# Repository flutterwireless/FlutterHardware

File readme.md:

Flutter Wireless Open Source Hardware files
==============

Flutter Wireless is an open source hardware platform designed by Taylor Alexander for the development of mesh networking protocols and connected devices. It is intended for use in robotics, hobbyist, commercial, or educational applications. For more information visit [FlutterWireless.com](http://www.flutterwireless.com/). All files copyright Flutter Wireless, 2013-2015.

Instructions
----------

If you want to modify these files, you need a version of EagleCAD that can work with 4 layer files (the freeware version only supports 2 layers). They have a [hobby license](http://www.cadsoftusa.com/shop/eagle-hobbyist-and-education/?lang=en) that is well-suited for this. If you only want to reproduce the boards as is, we have provided gerber files. Note that the files do not have a clean perimeter as they are intended to be arrayed on a panel. We will probably revert to a non panel-ready version at some point, as I don't believe our assembler needs them to be that way. Please file an issue if you cannot use them in their current format.

License
--------

This is the initial release of the hardware design files. They are licensed under Creative Commons Attribution-ShareAlike 4.0 International (CC BY-SA 4.0), which is available at: http://creativecommons.org/licenses/by-sa/4.0/
If you use the files, please check them carefully - they may contain errors.

Legal
--------

These documents are provided for informational purposes only and neither Flutter Wireless nor its employees, contributors, or representatives may be held liable for any damages caused by the use of these files. By using these files, you agree to release from all liability and hold harmless Flutter Wireless, its employees, contributors, and representatives. We are not responsible for any errors or ommissions contained herin, and all devices derived from this work should be indepentently verified by an engineer or engineers skilled in the appropriate fields.

The devices described by these files are wireless devices classified as intentional radiators. The electromagnetic spectrum used by these devices is a publicly shared medium that is regulated by all governments worldwide. If you produce your own copies of these boards, you must comply with all local wireless regulations including but not limited to passing wireless certification tests. Flutter Wireless has performed wireless testing to permit us to distribute this hardware in various regions, but this certification is exclusive to Flutter Wireless and does not extend to third party manufacturers. It is your responsibility to know the laws and ensure that devices you produce follow them.

It should also be noted that open source radio products are a new phenomenon. So far the law permits them, but there is a risk that new legal restrictions could be passed that harm the open source community if users abuse this hardware by producing versions of this or other hardware that violate the law. Be respectful and responsible - don't make changes that you don't understand or that violate the law. None of this should be considered legal advice - just common sense.

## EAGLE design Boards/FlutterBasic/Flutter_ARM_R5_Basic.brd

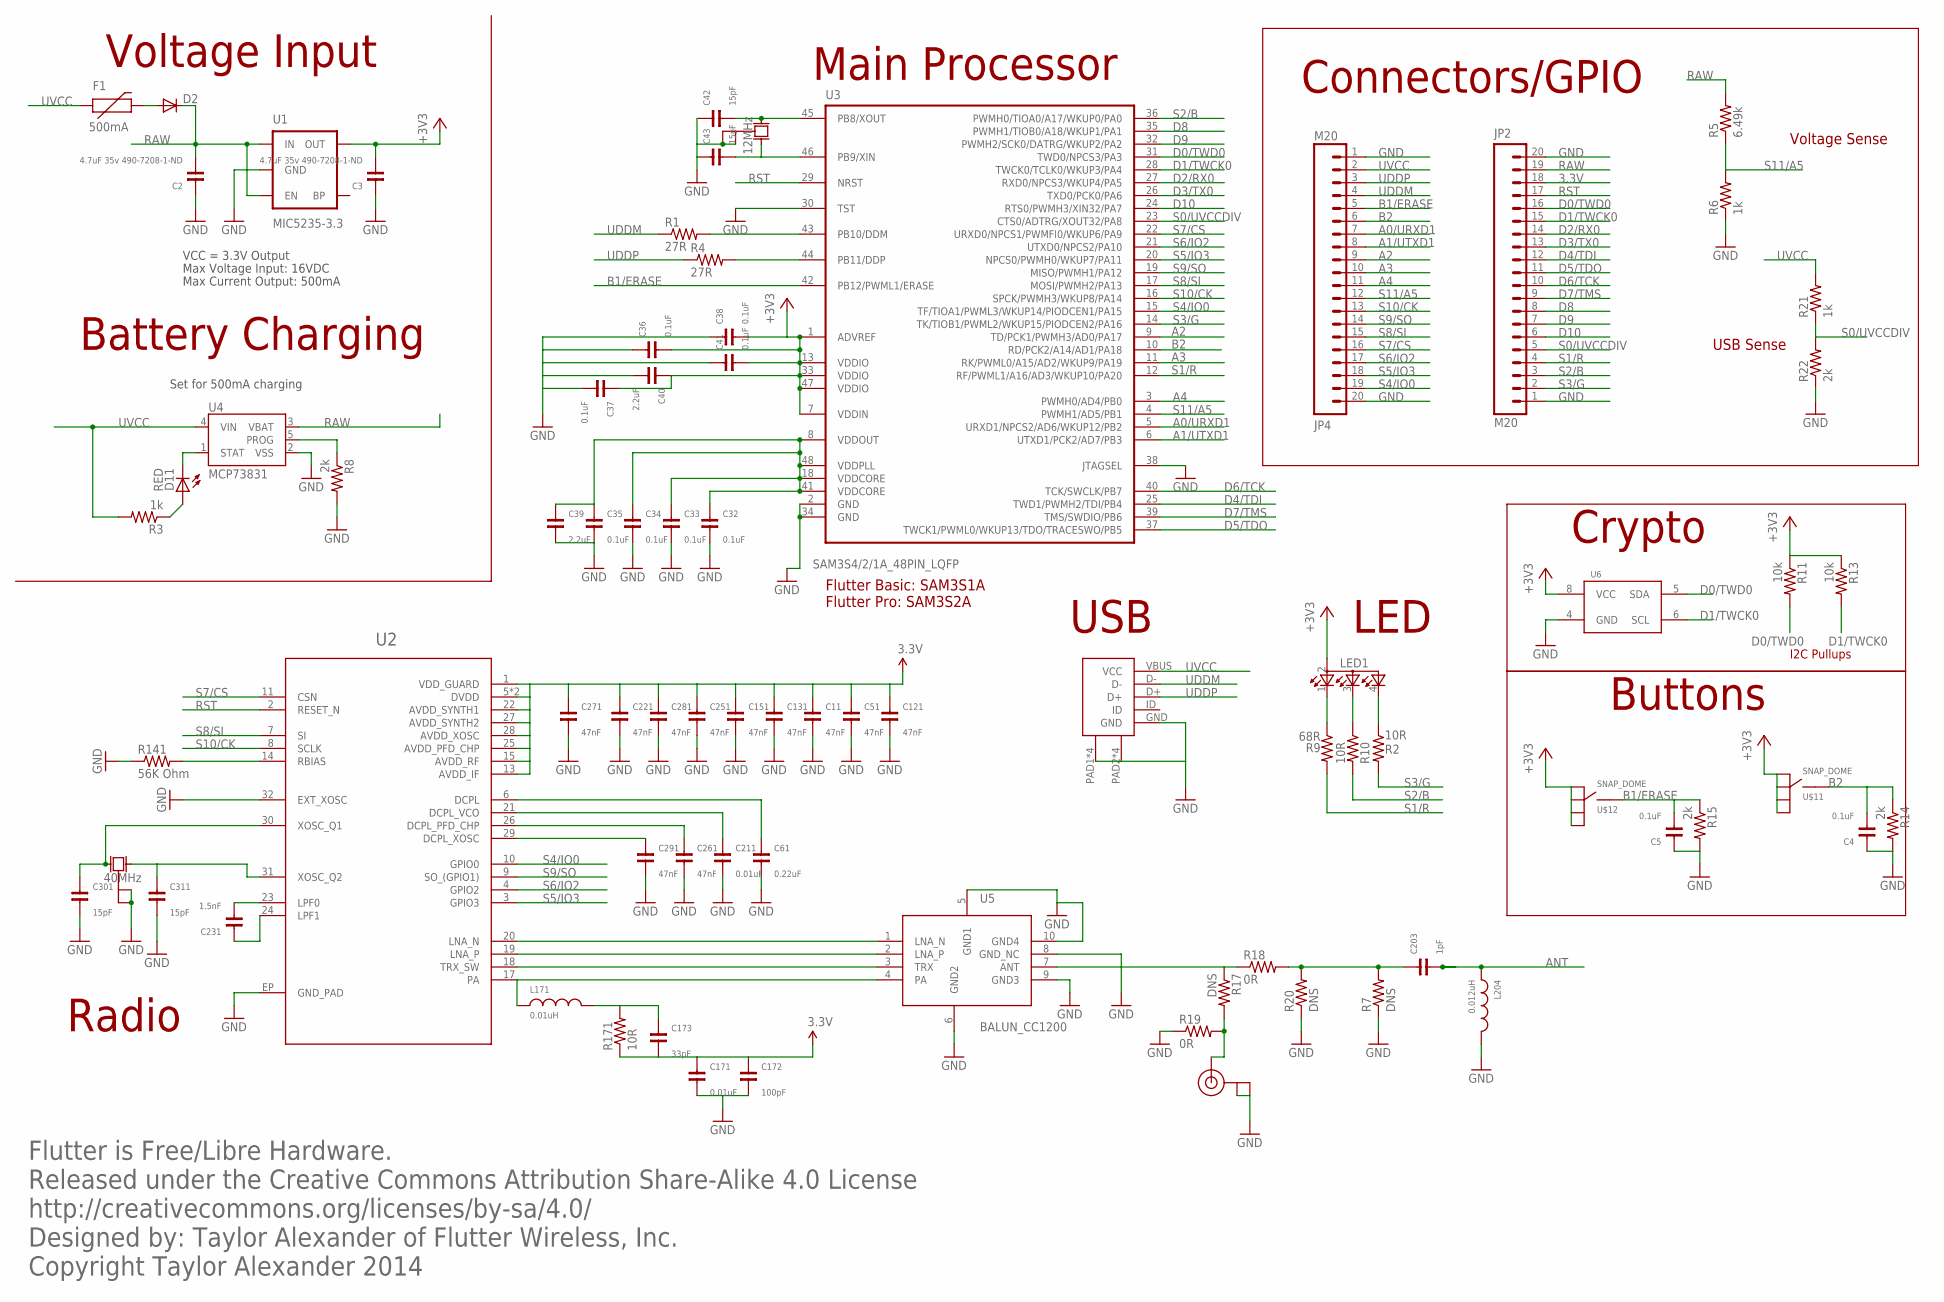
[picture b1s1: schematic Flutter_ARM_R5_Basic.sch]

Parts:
C2, C3: 4.7uF 35v 490-7208-1-ND; 0808-CAP
C4, C5, C32, C33, C34, C35, C36, C37, C38, C41: 0.1uF; 0402-CAP
C11, C51, C121, C131, C151, C221, C251, C261, C271, C281, C291: 47nF; 0402-CAP
C39, C40: 2.2uF; 0402-CAP
C42, C43, C301, C311: 15pF; 0402-CAP
C61: 0.22uF; 0402-CAP
C171, C211: 0.01uF; 0402-CAP
C172: 100pF; 0402-CAP
C173: 33pF; 0402-CAP
C203: 1pF; 0402-CAP
C231: 1.5nF; 0402-CAP
D2: DIODESOD; SOD-323
D11: RED; LED-0603
F1: 500mA; 0603-PTC
JP2, JP4: M20; 1X20
L171: 0.01uH; 0402-IND
L204: 0.012uH; 0402-IND
LED1: TOPLED-3; P-LCC-4-3
R1, R4: 27R; 0402-RES
R2, R10, R171: 10R; 0402-RES
R3, R6, R21: 1k; 0402-RES
R5: 6.49k; 0402-RES
R7, R17, R20: DNS; 0402-RES
R8, R14, R15, R22: 2k; 0402-RES
R9: 68R; 0402-RES
R11, R13: 10k; 0402-RES
R18, R19: 0R; 0402-RES
R141: 56K Ohm; 0402-RES
U1: MIC5235-3.3; SOT23-5
U2: CC1200; QFN-32
U3: SAM3S4/2/1A_48PIN_LQFP; LQFP48
U4: MCP73831; SOT23-5
U5: BALUN_CC1200; IPC_BALUN_CC1200
U6: ATSHA204/ATECC108UDFN; UDFN_8_ATSHA204
U7: U.FL
U$2: MICRO_USB; MICRO-USB-SLOT-2
U$11, U$12: SNAP_DOME; 12MM_SNAP_DOME_SMALLER
X1: 12MHz; XTAL_ABRACON_ABM8G_3.2MMX2.5MM
X2: 40MHz; XTAL_EPSON_FA_128_2MMX1.6MM

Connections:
3.3V: C3.2, C11.1, C36.2, C37.1, C38.2, C40.1, C41.2, C51.1, C121.1, C131.1, C151.1, C171.1, C172.1, C173.2, C221.1, C251.1, C271.1, C281.1, JP2.18, LED1.2 (A2), R11.1, R13.1, R171.1, U1.5 (OUT), U2.1 (VDD_GUARD), U2.5 (DVDD), U2.12 (DVDD), U2.13 (AVDD_IF), U2.15 (AVDD_RF), U2.22 (AVDD_SYNTH1), U2.25 (AVDD_PFD_CHP), U2.27 (AVDD_SYNTH2), U2.28 (AVDD_XOSC), U3.1 (ADVREF), U3.7 (VDDIN), U3.13 (VDDIO), U3.33 (VDDIO), U3.47 (VDDIO), U6.8 (VCC), U$11.P$1, U$11.P$2, U$11.P$3, U$11.P$4, U$12.P$1, U$12.P$2, U$12.P$3, U$12.P$4
+1.8V: C32.1, C33.1, C34.1, C35.1, C39.1, U3.8 (VDDOUT), U3.18 (VDDCORE), U3.41 (VDDCORE), U3.48 (VDDPLL)
A0/URXD1: JP4.7, U3.5 (URXD1/NPCS2/AD6/WKUP12/PB2)
A1/UTXD1: JP4.8, U3.6 (UTXD1/PCK2/AD7/PB3)
A2: JP4.9, U3.9 (TD/PCK1/PWMH3/AD0/PA17)
A3: JP4.10, U3.11 (RK/PWML0/A15/AD2/WKUP9/PA19)
A4: JP4.11, U3.3 (PWMH0/AD4/PB0)
ANT: C203.2, L204.1
B1/ERASE: C5.2, JP4.5, R15.1, U3.42 (PB12/PWML1/ERASE), U$12.CENTER
B2: C4.2, JP4.6, R14.1, U3.10 (RD/PCK2/A14/AD1/PA18), U$11.CENTER
D0/TWD0: JP2.16, R11.2, U3.31 (TWD0/NPCS3/PA3), U6.5 (SDA)
D1/TWCK0: JP2.15, R13.2, U3.28 (TWCK0/TCLK0/WKUP3/PA4), U6.6 (SCL)
D2/RX0: JP2.14, U3.27 (RXD0/NPCS3/WKUP4/PA5)
D3/TX0: JP2.13, U3.26 (TXD0/PCK0/PA6)
D4/TDI: JP2.12, U3.25 (TWD1/PWMH2/TDI/PB4)
D5/TDO: JP2.11, U3.37 (TWCK1/PWML0/WKUP13/TDO/TRACESWO/PB5)
D6/TCK: JP2.10, U3.40 (TCK/SWCLK/PB7)
D7/TMS: JP2.9, U3.39 (TMS/SWDIO/PB6)
D8: JP2.8, U3.35 (PWMH1/TIOB0/A18/WKUP1/PA1)
D9: JP2.7, U3.32 (PWMH2/SCK0/DATRG/WKUP2/PA2)
D10: JP2.6, U3.24 (RTS0/PWMH3/XIN32/PA7)
GND: C2.1, C3.1, C4.1, C5.1, C11.2, C32.2, C33.2, C34.2, C35.2, C36.1, C37.2, C38.1, C39.2, C40.2, C41.1, C42.1, C43.1, C51.2, C61.2, C121.2, C131.2, C151.2, C171.2, C172.2, C211.2, C221.2, C251.2, C261.2, C271.2, C281.2, C291.2, C301.2, C311.2, JP2.1, JP2.20, JP4.1, JP4.20, L204.2, R6.1, R7.1, R8.2, R14.2, R15.2, R19.1, R20.1, R22.1, R141.1, U1.2 (GND), U2.32 (EXT_XOSC), U2.EP (GND_PAD), U3.2 (GND), U3.30 (TST), U3.34 (GND), U3.38 (JTAGSEL), U4.2 (VSS), U5.5 (GND1), U5.6 (GND2), U5.8 (GND_NC), U5.9 (GND3), U5.10 (GND4), U6.4 (GND), U7.P$1 (GND), U7.P$2 (GND), U$2.GND, U$2.PAD1, U$2.PAD2, U$2.PAD3, U$2.PAD4, U$2.PAD5, U$2.PAD6, U$2.PAD7, U$2.PAD8, X1.P$2 (GND), X1.P$4 (GND), X2.2 (GND), X2.4 (GND)
LNA_N: U2.20 (LNA_N), U5.1 (LNA_N)
LNA_P: U2.19 (LNA_P), U5.2 (LNA_P)
unnamed: C61.1, U2.6 (DCPL)
unnamed: R141.2, U2.14 (RBIAS)
unnamed: C231.1, U2.24 (LPF1)
unnamed: C231.2, U2.23 (LPF0)
unnamed: C211.1, U2.21 (DCPL_VCO)
unnamed: D11.A, R3.1
unnamed: C173.1, L171.2, R171.2
unnamed: C203.1, R7.2, R18.2, R20.2
unnamed: D2.2 (A), F1.2
unnamed: R17.1, R18.1, U5.7 (ANT)
unnamed: R17.2, R19.2, U7.P$3 (SIGNAL)
unnamed: C311.1, U2.31 (XOSC_Q2), X2.1 (X1)
unnamed: C261.1, U2.26 (DCPL_PFD_CHP)
unnamed: C301.1, U2.30 (XOSC_Q1), X2.3 (X2)
unnamed: C291.1, U2.29 (DCPL_XOSC)
unnamed: LED1.1 (CRED), R9.1
unnamed: LED1.4 (CGREEN), R2.1
unnamed: C42.2, U3.45 (PB8/XOUT), X1.P$3 (X2)
unnamed: C43.2, U3.46 (PB9/XIN), X1.P$1 (X1)
PA: L171.1, U2.17 (PA), U5.4 (PA)
PROG: R8.1, U4.5 (PROG)
RAW: C2.2, D2.1 (C), JP2.19, R5.2, U1.1 (IN), U1.3 (EN), U4.3 (VBAT)
RST: JP2.17, U2.2 (RESET_N), U3.29 (NRST)
S0/UVCCDIV: JP2.5, R21.1, R22.2, U3.23 (CTS0/ADTRG/XOUT32/PA8)
S1/R: JP2.4, R9.2, U3.12 (RF/PWML1/A16/AD3/WKUP10/PA20)
S2/B: JP2.3, R10.2, U3.36 (PWMH0/TIOA0/A17/WKUP0/PA0)
S3/G: JP2.2, R2.2, U3.14 (TK/TIOB1/PWML2/WKUP15/PIODCEN2/PA16)
S4/IO0: JP4.19, U2.10 (GPIO0), U3.15 (TF/TIOA1/PWML3/WKUP14/PIODCEN1/PA15)
S5/IO3: JP4.18, U2.3 (GPIO3), U3.20 (NPCS0/PWMH0/WKUP7/PA11)
S6/IO2: JP4.17, U2.4 (GPIO2), U3.21 (UTXD0/NPCS2/PA10)
S7/CS: JP4.16, U2.11 (CSN), U3.22 (URXD0/NPCS1/PWMFI0/WKUP6/PA9)
S8/SI: JP4.15, U2.7 (SI), U3.17 (MOSI/PWMH2/PA13)
S9/SO: JP4.14, U2.9 (SO_(GPIO1)), U3.19 (MISO/PWMH1/PA12)
S10/CK: JP4.13, U2.8 (SCLK), U3.16 (SPCK/PWMH3/WKUP8/PA14)
S11/A5: JP4.12, R5.1, R6.2, U3.4 (PWMH1/AD5/PB1)
STAT: D11.C, U4.1 (STAT)
TRX_SW: U2.18 (TRX_SW), U5.3 (TRX)
U7: LED1.3 (CBLUE), R10.1
UDDC_+: R4.2, U3.44 (PB11/DDP)
UDDC_-: R1.2, U3.43 (PB10/DDM)
UDDM: JP4.4, R1.1, U$2.D-
UDDP: JP4.3, R4.1, U$2.D+
UVCC: F1.1, JP4.2, R3.2, R21.2, U4.4 (VIN), U$2.VBUS (VCC)

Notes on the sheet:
Max Voltage Input: 16VDC
Max Current Output: 500mA
VCC = 3.3V Output
Flutter is Free/Libre Hardware. Released under the Creative Commons Attribution Share-Alike 4.0 License http://creativecommons.org/licenses/by-sa/4.0/ Designed by: Taylor Alexander of Flutter Wireless, Inc. Copyright Taylor Alexander 2014
I2C Pullups
Set for 500mA charging
Voltage Input
Battery Charging
Main Processor
Connectors/GPIO
Radio
Buttons
Crypto
USB
LED
Flutter Basic: SAM3S1A Flutter Pro: SAM3S2A
Voltage Sense
USB Sense

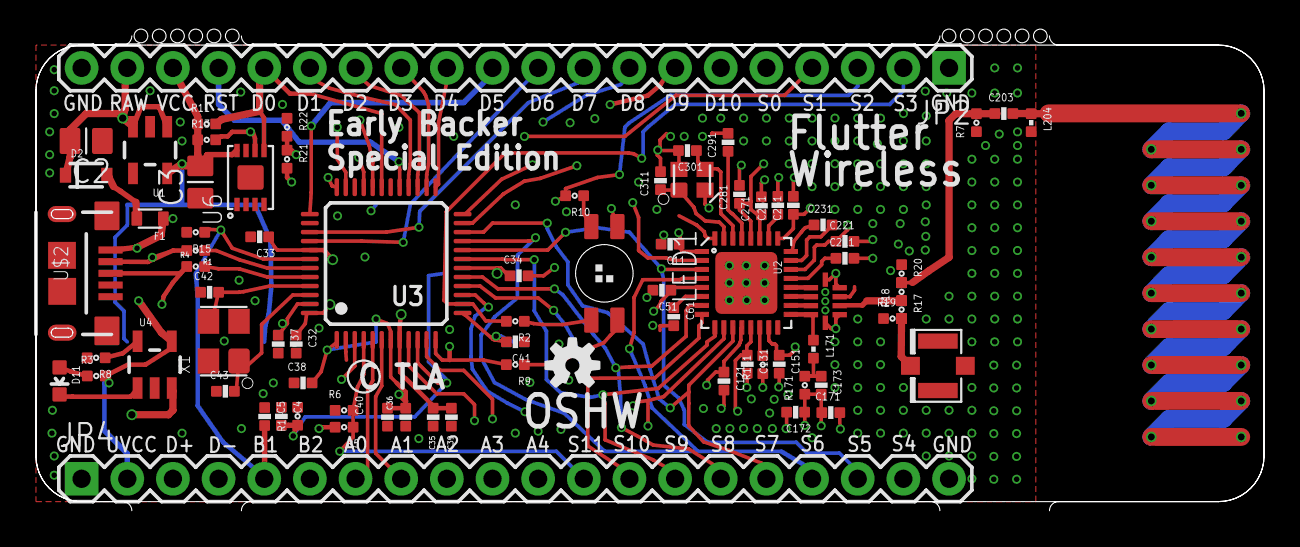
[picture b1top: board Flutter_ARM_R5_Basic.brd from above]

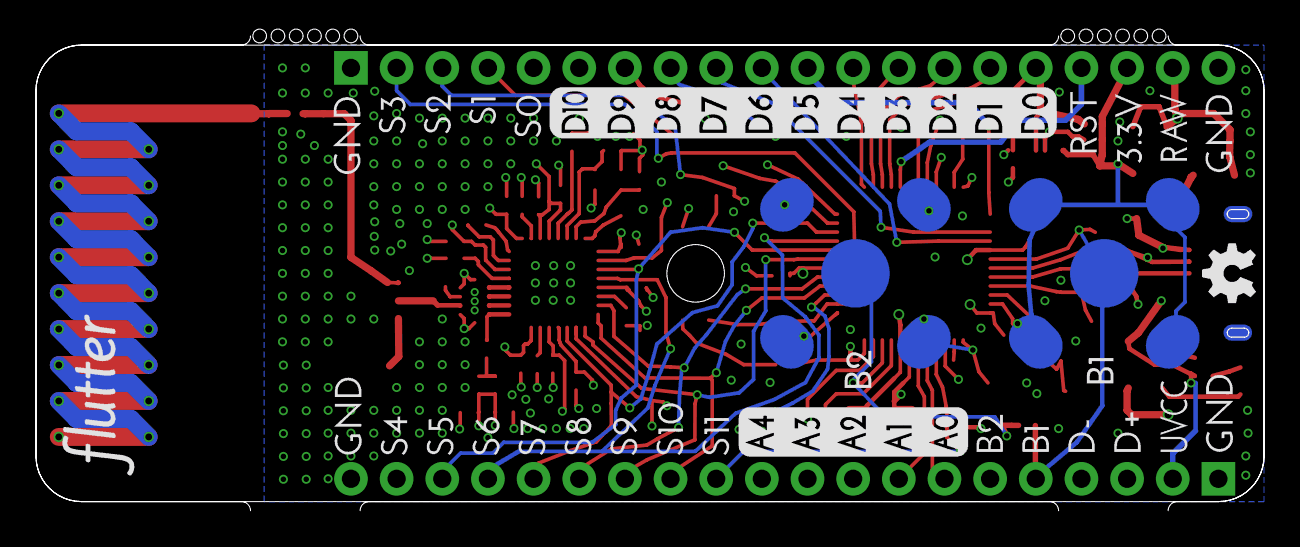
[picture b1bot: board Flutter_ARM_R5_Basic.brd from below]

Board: 4 copper layers, 68.3 x 26.4 mm, 79 parts (2 on the bottom side), 67 nets.

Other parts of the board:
U$1: OSHW-LOGOS; OSHW-LOGO-S

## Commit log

2014-11-26 initial commit, Flutter Wireless first release.
2014-11-27 update readme. added copyright and basic instructions
2015-03-27 Reorganized schematic, generated PDF schematic.
2015-03-27 Added version number, changed schematic name.
2015-03-27 Re-added schematic PDF, which was left out last commit.
2015-03-27 Removed spaces from schematic name for nicer URL.

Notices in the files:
parts and their libraries:
SparkFun-Aesthetics: Licensing: CC v3.0 Share-Alike You are welcome to use this library for commercial purposes.
